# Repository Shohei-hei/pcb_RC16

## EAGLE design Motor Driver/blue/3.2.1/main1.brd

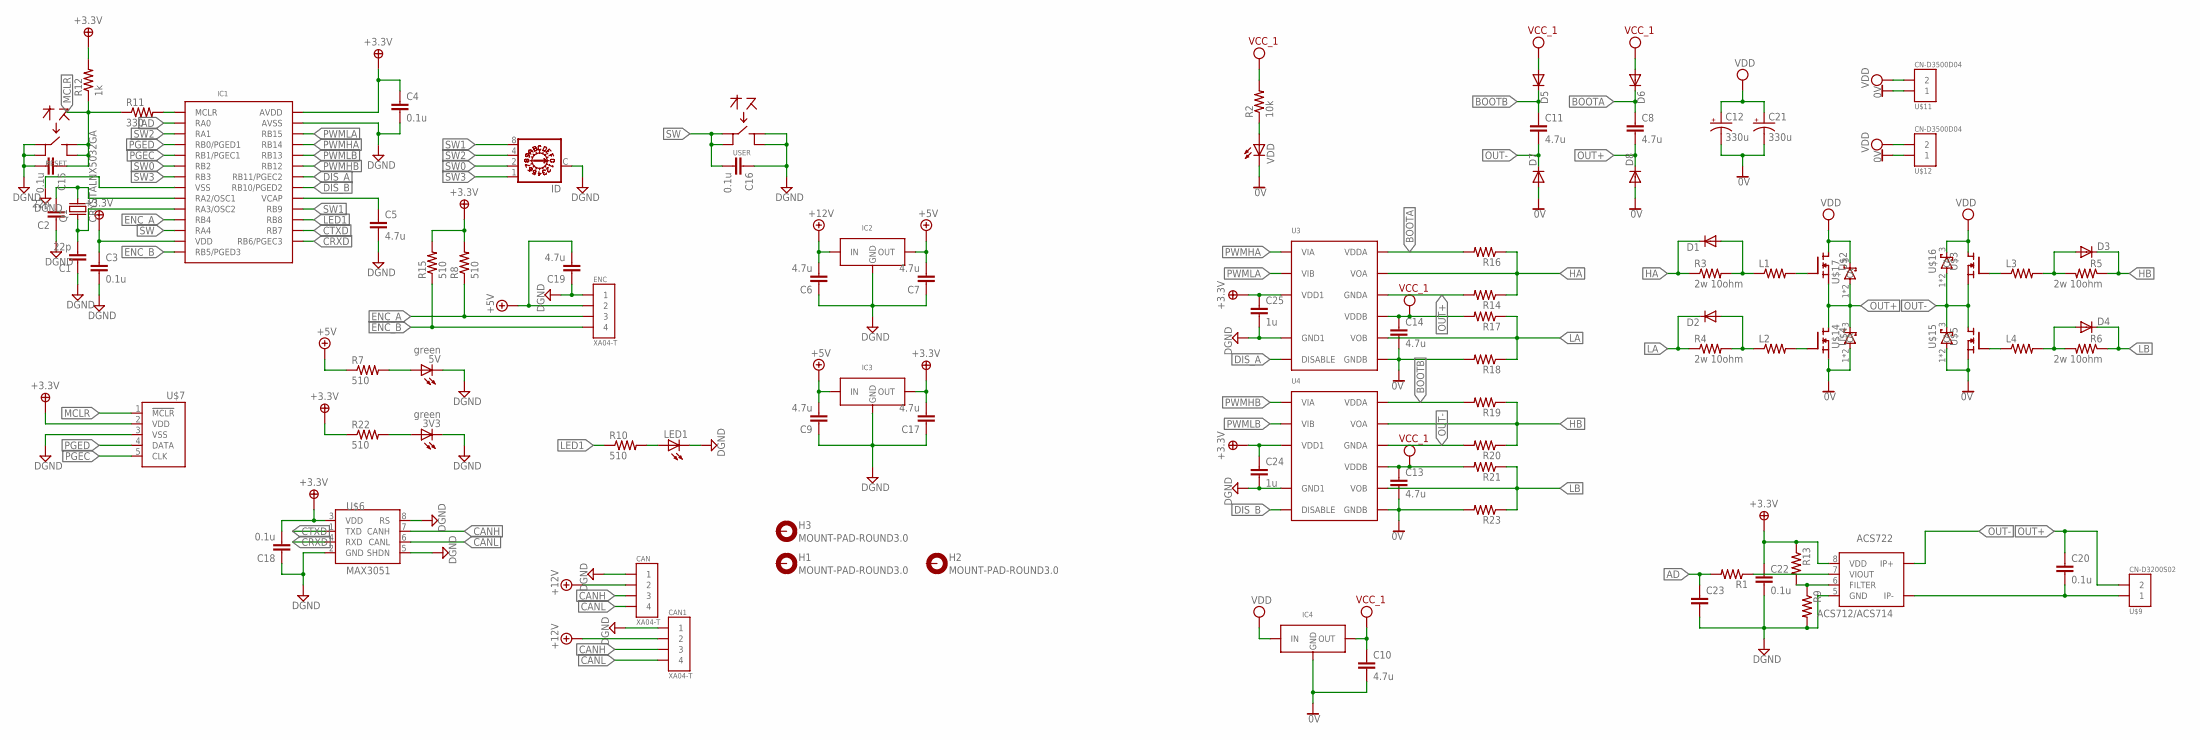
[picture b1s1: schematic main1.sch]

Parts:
3V3, 5V: green; CHIPLED_0603
ACS722: ACS712/ACS714; SOIC8
C1, C2: 22p; C0603K
C3, C4, C15, C16, C18, C20: 0.1u; C0603K
C5, C6, C7, C8, C9, C10, C11, C13, C14, C17, C19: 4.7u; C0805K
C12, C21: 330u; PANASONIC_G
C22: 0.1u; C1206
C23: C-EUC0603K; C0603K
C24, C25: 1u; C0603K
CAN, CAN1: XA04-T; XA04
D1, D2, D3, D4, D5, D6, D7, D8: DIODE-SOD123; SOD123
ENC: XA04-T; XA04
H1, H2, H3: MOUNT-PAD-ROUND3.0; 3,0-PAD
IC1: DSPIC33FJ128MC802; SOIC28
IC2: REGULATER_MIC39100-5.0WS; SOT-223
IC3: REGULATER_AZ1117CR; SOT89
IC4: REGULATER_MIC2940A-5.0WU; TO-263-3
ID: A1353HEX
L1, L2, L3, L4: R-US_R0805; R0805
LED1: LEDCHIPLED_0603; CHIPLED_0603
Q1: CRYSTALNX5032GA; NX5032GA
R1, R9, R13, R14, R16, R17, R18, R19, R20, R21, R23: R-US_R0603; R0603
R2: 10k; R0603
R3, R4, R5, R6: 2w 10ohm; R2512
R7, R8, R10, R15, R22: 510; R0603
R11: 330; R0603
R12: 1k; R0603
RESET: SWITCH_4PALPS; SKRP
U3, U4: ADUM3223_SMD; SOIC16_N
U$1: CN-D3500D04; D-3500D04
U$2, U$3, U$4, U$5: FET_NCH_FDMS86152; PQFN_8L
U$6: MAX3051; SOIC8
U$7: WRITE_FOR_PICT; ZH05
U$9: CN-D3200S02; D-3200S02-S
U$14, U$15, U$16, U$17: SCHOTTKY_BARRIER_DIODE_FSV560; TO-277
USER: SWITCH_4PALPS; SKRP
VDD: LEDCHIPLED_0603; CHIPLED_0603

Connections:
0V: C10.2, C12.-, C13.2, C14.2, C21.-, D7.A, D8.A, IC4.2 (GND), IC4.PAD (GND), R18.2, R23.2, U3.P$9 (GNDB), U4.P$9 (GNDB), U$1.01A (1), U$1.02A (1), U$4.1 (S), U$4.2 (S), U$4.3 (S), U$5.1 (S), U$5.2 (S), U$5.3 (S), U$14.1 (A), U$14.2 (A), U$15.1 (A), U$15.2 (A), VDD.C
3.3V: ACS722.8 (VDD), C3.1, C4.1, C17.2, C18.2, C22.1, C24.1, C25.1, IC1.13 (VDD), IC1.28 (AVDD), IC3.2 (OUT), IC3.P (OUT), R8.2, R12.2, R13.1, R15.2, R22.1, U3.P$3 (VDD1), U3.P$8 (VDD1), U4.P$3 (VDD1), U4.P$8 (VDD1), U$6.3 (VDD), U$7.2 (VDD)
+5V: C7.2, C9.2, C19.2, ENC.PIN2 (2), IC2.3 (OUT), IC3.3 (IN), R7.1
+12V: C6.2, CAN.PIN2 (2), CAN1.PIN2 (2), IC2.1 (IN)
AD: C23.1, IC1.2 (RA0), R1.2
BOOTA: C8.1, D6.C, R16.2, U3.P$16 (VDDA)
BOOTB: C11.1, D5.C, R19.2, U4.P$16 (VDDA)
CANH: CAN.PIN3 (3), CAN1.PIN3 (3), U$6.7 (CANH)
CANL: CAN.PIN4 (4), CAN1.PIN4 (4), U$6.6 (CANL)
CRXD: IC1.15 (RB6/PGEC3), U$6.4 (RXD)
CTXD: IC1.16 (RB7), U$6.1 (TXD)
DGND: 3V3.C, 5V.C, ACS722.5 (GND), C1.1, C2.1, C3.2, C4.2, C5.2, C6.1, C7.1, C9.1, C15.2, C16.1, C17.1, C18.1, C19.1, C22.2, C23.2, C24.2, C25.2, CAN.PIN1 (1), CAN1.PIN1 (1), ENC.PIN1 (1), IC1.8 (VSS), IC1.19 (VSS), IC1.27 (AVSS), IC2.2 (GND), IC2.TAB (GND), IC3.1 (GND), ID.C, LED1.C, R9.2, RESET.1, RESET.2, U3.P$4 (GND1), U4.P$4 (GND1), U$6.2 (GND), U$6.5 (SHDN), U$6.8 (RS), U$7.3 (VSS), USER.3, USER.4
DIS_A: IC1.22 (RB11/PGEC2), U3.P$5 (DISABLE)
DIS_B: IC1.21 (RB10/PGED2), U4.P$5 (DISABLE)
ENC_A: ENC.PIN3 (3), IC1.11 (RB4), R8.1
ENC_B: ENC.PIN4 (4), IC1.14 (RB5/PGED3), R15.1
HA: D1.C, R3.1, R14.1, R16.1, U3.P$15 (VOA)
HB: D3.C, R5.1, R19.1, R20.1, U4.P$15 (VOA)
LA: D2.C, R4.1, R17.1, R18.1, U3.P$10 (VOB)
LB: D4.C, R6.1, R21.1, R23.1, U4.P$10 (VOB)
LED1: IC1.17 (RB8), R10.1
MCLR: C15.1, R11.1, R12.1, RESET.3, RESET.4, U$7.1 (!MCLR)
unnamed: C2.2, IC1.9 (RA2/OSC1), Q1.2
unnamed: C1.2, IC1.10 (RA3/OSC2), Q1.1
unnamed: C5.1, IC1.20 (VCAP)
unnamed: L2.2, U$4.4 (G)
unnamed: R2.1, VDD.A
unnamed: ACS722.7 (VIOUT), R1.1
unnamed: LED1.A, R10.2
unnamed: D1.A, L1.1, R3.2
unnamed: D2.A, L2.1, R4.2
unnamed: 5V.A, R7.2
unnamed: L4.1, U$5.4 (G)
unnamed: D4.A, L4.2, R6.2
unnamed: L3.1, U$3.4 (G)
unnamed: D3.A, L3.2, R5.2
unnamed: ACS722.3 (IP-), ACS722.4 (IP-), C20.2, U$9.1, U$9.P$1 (1)
unnamed: IC1.1 (MCLR), R11.2
unnamed: ACS722.6 (FILTER), R9.1, R13.2
unnamed: 3V3.A, R22.2
unnamed: L1.2, U$2.4 (G)
OUT+: C8.2, C20.1, D8.C, R14.2, U3.P$14 (GNDA), U$2.1 (S), U$2.2 (S), U$2.3 (S), U$4.5 (D), U$4.6 (D), U$4.7 (D), U$4.8 (D), U$4.PAD (D), U$9.2, U$9.P$2 (2), U$14.3 (C), U$17.1 (A), U$17.2 (A)
OUT-: ACS722.1 (IP+), ACS722.2 (IP+), C11.2, D7.C, R20.2, U4.P$14 (GNDA), U$3.1 (S), U$3.2 (S), U$3.3 (S), U$5.5 (D), U$5.6 (D), U$5.7 (D), U$5.8 (D), U$5.PAD (D), U$15.3 (C), U$16.1 (A), U$16.2 (A)
PGEC: IC1.5 (RB1/PGEC1), U$7.5 (CLK)
PGED: IC1.4 (RB0/PGED1), U$7.4 (DATA)
PWMHA: IC1.25 (RB14), U3.P$1 (VIA)
PWMHB: IC1.23 (RB12), U4.P$1 (VIA)
PWMLA: IC1.26 (RB15), U3.P$2 (VIB)
PWMLB: IC1.24 (RB13), U4.P$2 (VIB)
SW: C16.2, IC1.12 (RA4), USER.1, USER.2
SW0: IC1.6 (RB2), ID.2
SW1: IC1.18 (RB9), ID.8
SW2: IC1.3 (RA1), ID.4
SW3: IC1.7 (RB3), ID.1
VCC_1: C10.1, C13.1, C14.1, D5.A, D6.A, IC4.3 (OUT), R2.2, R17.2, R21.2, U3.P$11 (VDDB), U4.P$11 (VDDB)
VDD: C12.+, C21.+, IC4.1 (IN), U$1.01B (2), U$1.02B (2), U$2.5 (D), U$2.6 (D), U$2.7 (D), U$2.8 (D), U$2.PAD (D), U$3.5 (D), U$3.6 (D), U$3.7 (D), U$3.8 (D), U$3.PAD (D), U$16.3 (C), U$17.3 (C)

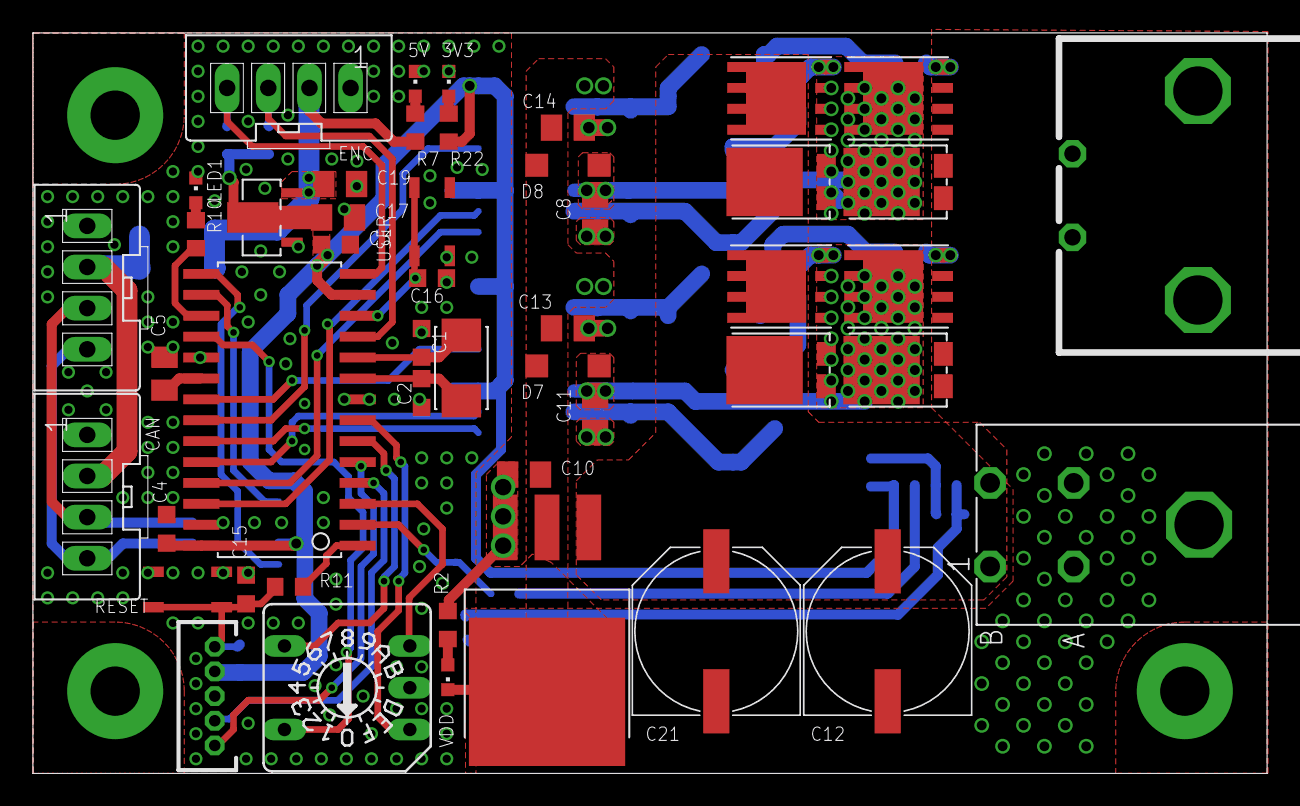
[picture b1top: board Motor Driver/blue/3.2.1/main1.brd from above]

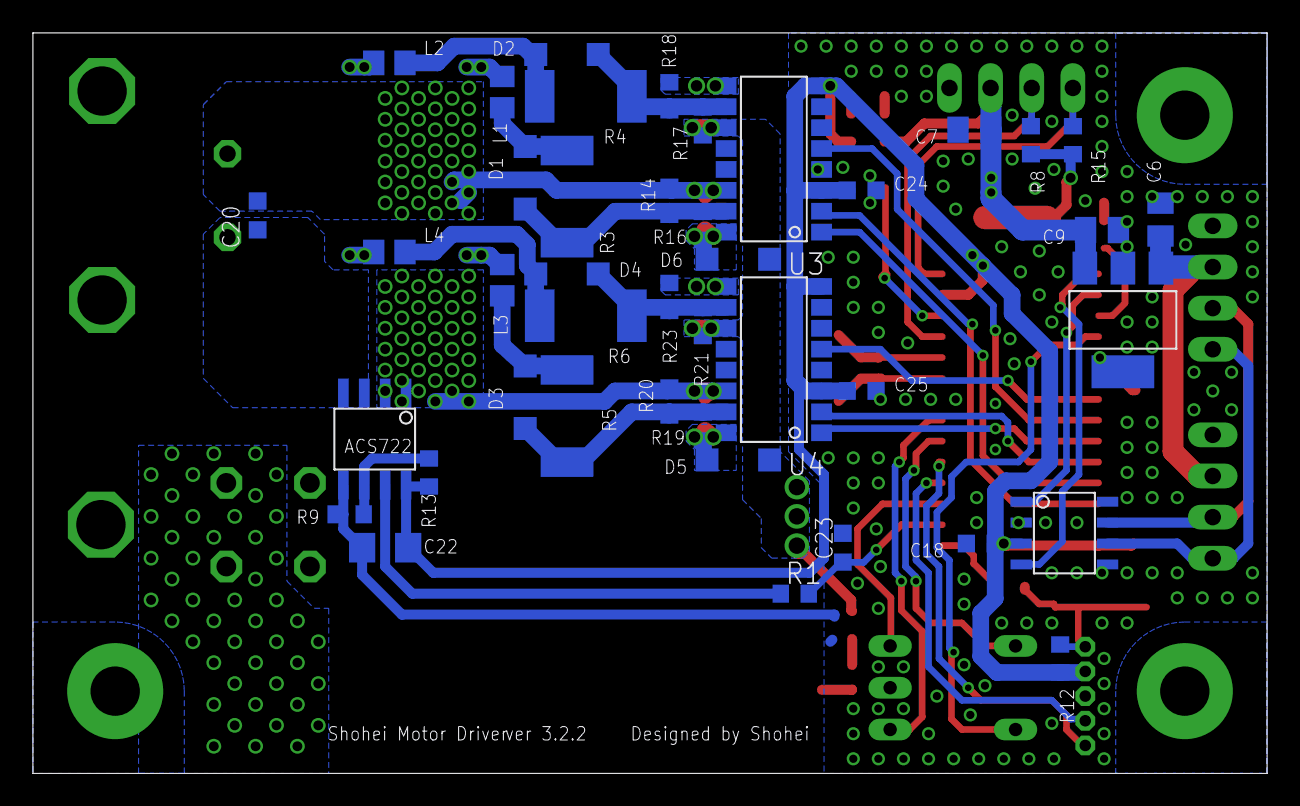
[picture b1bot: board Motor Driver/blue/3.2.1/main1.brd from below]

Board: 2 copper layers, 75.0 x 45.0 mm, 93 parts (42 on the bottom side), 56 nets.

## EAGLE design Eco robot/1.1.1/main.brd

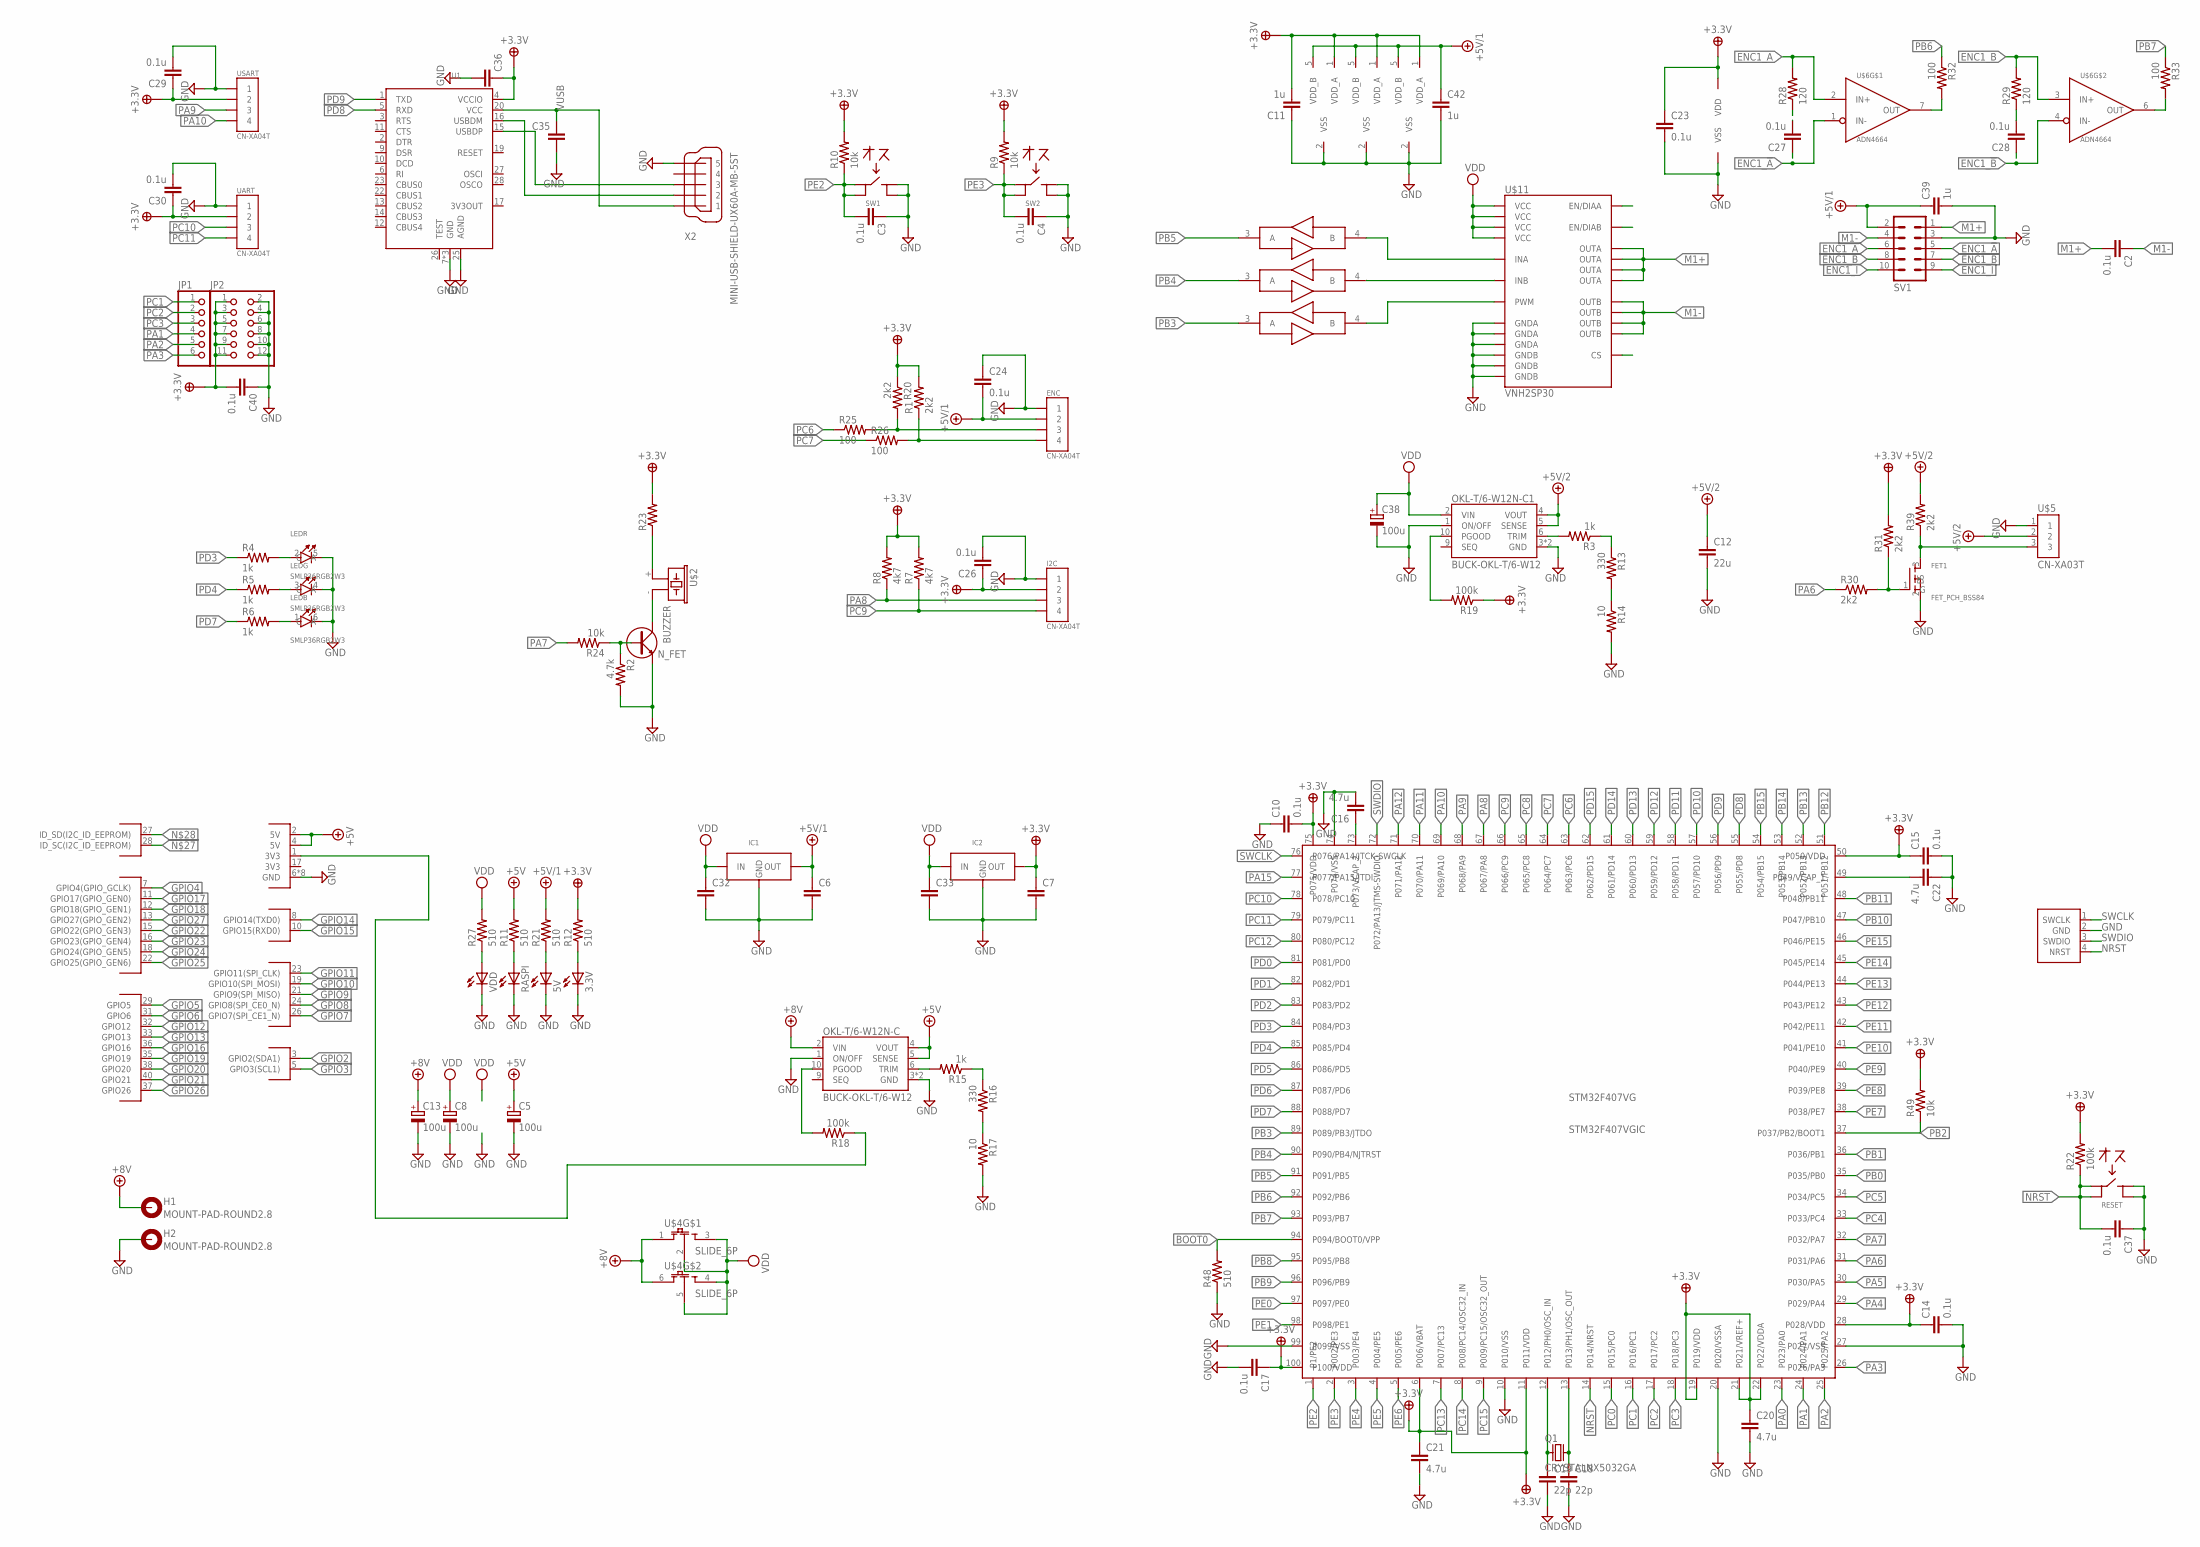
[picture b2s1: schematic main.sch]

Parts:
3.3V, 5V: LEDCHIPLED_0603; CHIPLED_0603
C2, C3, C4, C10, C14, C15, C17, C23, C27, C28, C37: 0.1u; C0603K
C5, C13: 100u; PANASONIC_C
C6, C7, C32, C33: C-EUC0805K; C0805K
C8, C38: 100u; PANASONIC_D
C11, C39, C42: 1u; C0603K
C12: 22u; C0805K
C16, C20, C21, C22: 4.7u; C0805K
C18, C19: 22p; C0603K
C24, C26, C29, C30: 0.1u; C0805
C35, C36: C-EUC0603K; C0603K
C40: 0.1u; C0805K
ENC: CN-XA04T; XA04
FET1: FET_PCH_BSS84; SOT-23-3
H1, H2: MOUNT-PAD-ROUND2.8; 2,8-PAD
I2C: CN-XA04T; XA04
IC1, IC2: REGULATERLM1058; SOT-223
JP1: PINHD-1X06_2.54-S; 1X06-S
JP2: PINHD-2X06_2.54; 2X06
LED: SMLP36RGB2W3; 0604(6PIN)
N_FET: TR_NTR; SOT-23-3
OKL-T/6-W12N-C, OKL-T/6-W12N-C1: BUCK-OKL-T/6-W12
Q1: CRYSTALNX5032GA; NX5032GA
R1, R20, R30, R31, R39: 2k2; R0603
R2: 4.7k; R0603
R3, R15: 1k; R0603
R4, R5, R6: 1k; R0402
R7, R8: 4k7; R0603
R9, R10, R24, R49: 10k; R0603
R11, R12, R21, R27, R48: 510; R0603
R13, R16: 330; R0603
R14, R17: 10; R0603
R18, R19, R22: 100k; R0603
R23: R-US_R0603; R0603
R25, R26, R32, R33: 100; R0603
R28, R29: 120; R0603
RASPI: LEDCHIPLED_0603; CHIPLED_0603
RESET: SWITCH_4PALPS; SKRP
STM32F407VG: STM32F407VGIC; LQFP100
SV1: ML10_T; ML10
SW1, SW2: SWITCH_4PALPS; SKRP
U1: FT232RL; SSOP28
U$1: RASPBERRY_PAI2_B; PAI_2_B_RS
U$2: BUZZER; SMT-0440-S-R
U$3: WRITE_FOR_STM32FXT; ZH05
U$4: SLIDE_6P; SSW-SMD
U$5: CN-XA03T; XA03
U$6: ADN4664; SOIC8
U$7, U$9, U$10: MAX3370; SOT-353/SC-70-5
U$11: VNH2SP30
UART: CN-XA04T; XA04
USART: CN-XA04T; XA04
VDD: LEDCHIPLED_0603; CHIPLED_0603
X2: MINI-USB-SHIELD-UX60A-MB-5ST; UX60A-MB-5ST

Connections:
3.3V: C7.1, C10.2, C11.2, C14.1, C15.1, C17.1, C20.1, C21.1, C23.1, C26.1, C29.1, C30.1, C36.1, C40.2, I2C.PIN2 (2), IC2.2 (OUT), IC2.4 (OUT), JP2.1, JP2.3, JP2.5, JP2.7, JP2.9, JP2.11, R1.2, R7.2, R8.2, R9.2, R10.2, R12.2, R19.1, R20.1, R22.2, R23.2, R31.2, R49.2, STM32F407VG.6 (P006/VBAT), STM32F407VG.11 (P011/VDD), STM32F407VG.19 (P019/VDD), STM32F407VG.21 (P021/VREF+), STM32F407VG.22 (P022/VDDA), STM32F407VG.28 (P028/VDD), STM32F407VG.50 (P050/VDD), STM32F407VG.75 (P075/VDD), STM32F407VG.100 (P100/VDD), U1.4 (VCCIO), U$6.8 (VDD), U$7.1 (VDD_A), U$9.1 (VDD_A), U$10.1 (VDD_A), UART.PIN2 (2), USART.PIN2 (2)
+5V: C5.+, OKL-T/6-W12N-C.4 (VOUT), OKL-T/6-W12N-C.5 (SENSE), R11.2, U$1.2 (5V), U$1.4 (5V)
+5V/1: C6.1, C24.2, C39.1, C42.1, ENC.PIN2 (2), IC1.2 (OUT), IC1.4 (OUT), R21.2, SV1.2, U$7.5 (VDD_B), U$9.5 (VDD_B), U$10.5 (VDD_B)
+5V/2: C12.1, OKL-T/6-W12N-C1.4 (VOUT), OKL-T/6-W12N-C1.5 (SENSE), R39.2, U$5.2
+8V: C13.+, H1.B2,8, OKL-T/6-W12N-C.2 (VIN), U$4.1, U$4.6
BOOT0: R48.2, STM32F407VG.94 (P094/BOOT0/VPP)
ENC1_!A: C27.1, SV1.5, U$6.1 (IN-)
ENC1_!B: C28.1, SV1.7, U$6.4 (IN-)
ENC1_!I: SV1.9
ENC1_A: R28.2, SV1.6, U$6.2 (IN+)
ENC1_B: R29.2, SV1.8, U$6.3 (IN+)
ENC1_I: SV1.10
GND: 3.3V.C, 5V.C, C3.1, C4.1, C5.-, C6.2, C7.2, C8.-, C10.1, C11.1, C12.2, C13.-, C14.2, C15.2, C16.2, C17.2, C18.2, C19.2, C20.2, C21.2, C22.1, C23.2, C24.1, C26.2, C29.2, C30.2, C32.2, C33.2, C35.2, C36.2, C37.1, C38.-, C39.2, C40.1, C42.2, ENC.PIN1 (1), FET1.2 (S), H2.B2,8, I2C.PIN1 (1), IC1.1 (GND), IC2.1 (GND), JP2.2, JP2.4, JP2.6, JP2.8, JP2.10, JP2.12, LED.4 (C), LED.5 (C), LED.6 (C), N_FET.2 (E), OKL-T/6-W12N-C.1 (ON/OFF), OKL-T/6-W12N-C.3 (GND), OKL-T/6-W12N-C.7 (GND), OKL-T/6-W12N-C1.1 (ON/OFF), OKL-T/6-W12N-C1.3 (GND), OKL-T/6-W12N-C1.7 (GND), R2.2, R14.2, R17.2, R48.1, RASPI.C, RESET.3, RESET.4, STM32F407VG.10 (P010/VSS), STM32F407VG.20 (P020/VSSA), STM32F407VG.27 (P027/VSS), STM32F407VG.74 (P074/VSS), STM32F407VG.99 (P099/VSS), SV1.3, SW1.3, SW1.4, SW2.3, SW2.4, U1.7 (GND), U1.18 (GND), U1.21 (GND), U1.25 (AGND), U$1.6 (GND), U$1.9 (GND), U$1.14 (GND), U$1.20 (GND), U$1.25 (GND), U$1.30 (GND), U$1.34 (GND), U$1.39 (GND), U$3.2 (GND), U$5.1, U$6.5 (VSS), U$7.2 (VSS), U$9.2 (VSS), U$10.2 (VSS), U$11.18 (GNDB), U$11.19 (GNDB), U$11.20 (GNDB), U$11.26 (GNDA), U$11.27 (GNDA), U$11.28 (GNDA), UART.PIN1 (1), USART.PIN1 (1), VDD.C, X2.5
GPIO2: U$1.3 (GPIO2(SDA1))
GPIO3: U$1.5 (GPIO3(SCL1))
GPIO4: U$1.7 (GPIO4(GPIO_GCLK))
GPIO5: U$1.29 (GPIO5)
GPIO6: U$1.31 (GPIO6)
GPIO7: U$1.26 (GPIO7(SPI_CE1_N))
GPIO8: U$1.24 (GPIO8(SPI_CE0_N))
GPIO9: U$1.21 (GPIO9(SPI_MISO))
GPIO10: U$1.19 (GPIO10(SPI_MOSI))
GPIO11: U$1.23 (GPIO11(SPI_CLK))
GPIO12: U$1.32 (GPIO12)
GPIO13: U$1.33 (GPIO13)
GPIO14: U$1.8 (GPIO14(TXD0))
GPIO15: U$1.10 (GPIO15(RXD0))
GPIO16: U$1.36 (GPIO16)
GPIO17: U$1.11 (GPIO17(GPIO_GEN0))
GPIO18: U$1.12 (GPIO18(GPIO_GEN1))
GPIO19: U$1.35 (GPIO19)
GPIO20: U$1.38 (GPIO20)
GPIO21: U$1.40 (GPIO21)
GPIO22: U$1.15 (GPIO22(GPIO_GEN3))
GPIO23: U$1.16 (GPIO23(GPIO_GEN4))
GPIO24: U$1.18 (GPIO24(GPIO_GEN5))
GPIO25: U$1.22 (GPIO25(GPIO_GEN6))
GPIO26: U$1.37 (GPIO26)
GPIO27: U$1.13 (GPIO27(GPIO_GEN2))
M1+: C2.2, SV1.1, U$11.1 (OUTA), U$11.25 (OUTA), U$11.30 (OUTA), U$11.SLUG3 (OUTA)
M1-: C2.1, SV1.4, U$11.15 (OUTB), U$11.16 (OUTB), U$11.21 (OUTB), U$11.SLUG2 (OUTB)
unnamed: ENC.PIN3 (3), R20.2, R25.2
unnamed: OKL-T/6-W12N-C1.6 (TRIM), R3.2
unnamed: LED.2 (A), R4.2
unnamed: LED.3 (A), R5.2
unnamed: LED.1 (A), R6.2
unnamed: N_FET.3 (C), U$2.- (2)
unnamed: C16.1, STM32F407VG.73 (P073/VCAP_2)
unnamed: R23.1, U$2.+ (1)
unnamed: R11.1, RASPI.A
unnamed: R3.1, R13.1
unnamed: N_FET.1 (B), R2.1, R24.1
unnamed: C27.2, R28.1
unnamed: OKL-T/6-W12N-C.6 (TRIM), R15.2
unnamed: R13.2, R14.1
unnamed: 3.3V.A, R12.1
unnamed: U$7.4 (B), U$11.8 (PWM)
unnamed: U1.15 (USBDP), X2.3
unnamed: ENC.PIN4 (4), R1.1, R26.2
unnamed: U1.16 (USBDM), X2.2
unnamed: R15.1, R16.1
unnamed: U$9.4 (B), U$11.11 (INB)
unnamed: R16.2, R17.1
unnamed: OKL-T/6-W12N-C.10 (PGOOD), R18.2
unnamed: C22.2, STM32F407VG.49 (P049/VCAP_1)
unnamed: 5V.A, R21.1
unnamed: R27.1, VDD.A
unnamed: C28.2, R29.1
unnamed: OKL-T/6-W12N-C1.10 (PGOOD), R19.2
unnamed: U$10.4 (B), U$11.5 (INA)
unnamed: FET1.3 (D), R39.1, U$5.3
unnamed: FET1.1 (G), R30.2, R31.1
unnamed: R18.1, U$1.1 (3V3)
unnamed: R32.2, U$6.7 (OUT)
unnamed: R33.2, U$6.6 (OUT)
NRST: C37.2, R22.1, RESET.1, RESET.2, STM32F407VG.14 (P014/NRST), U$3.4 (NRST)
PA0: STM32F407VG.23 (P023/PA0)
PA1: JP1.4, STM32F407VG.24 (P024/PA1)
PA2: JP1.5, STM32F407VG.25 (P025/PA2)
PA3: JP1.6, STM32F407VG.26 (P026/PA3)
PA4: STM32F407VG.29 (P029/PA4)
PA5: STM32F407VG.30 (P030/PA5)
PA6: R30.1, STM32F407VG.31 (P031/PA6)
PA7: R24.2, STM32F407VG.32 (P032/PA7)
PA8: I2C.PIN3 (3), R8.1, STM32F407VG.67 (P067/PA8)
PA9: STM32F407VG.68 (P068/PA9), USART.PIN3 (3)
PA10: STM32F407VG.69 (P069/PA10), USART.PIN4 (4)
PA11: STM32F407VG.70 (P070/PA11)
PA12: STM32F407VG.71 (P071/PA12)
PA15: STM32F407VG.77 (P077/PA15/JTDI)
PB0: STM32F407VG.35 (P035/PB0)
PB1: STM32F407VG.36 (P036/PB1)
PB2: R49.1, STM32F407VG.37 (P037/PB2/BOOT1)
PB3: STM32F407VG.89 (P089/PB3/JTDO), U$7.3 (A)
PB4: STM32F407VG.90 (P090/PB4/NJTRST), U$9.3 (A)
PB5: STM32F407VG.91 (P091/PB5), U$10.3 (A)
PB6: R32.1, STM32F407VG.92 (P092/PB6)
PB7: R33.1, STM32F407VG.93 (P093/PB7)
PB8: STM32F407VG.95 (P095/PB8)
PB9: STM32F407VG.96 (P096/PB9)
PB10: STM32F407VG.47 (P047/PB10)
PB11: STM32F407VG.48 (P048/PB11)
PB12: STM32F407VG.51 (P051/PB12)
PB13: STM32F407VG.52 (P052/PB13)
PB14: STM32F407VG.53 (P053/PB14)
PB15: STM32F407VG.54 (P054/PB15)
PC0: STM32F407VG.15 (P015/PC0)
PC1: JP1.1, STM32F407VG.16 (P016/PC1)
PC2: JP1.2, STM32F407VG.17 (P017/PC2)
PC3: JP1.3, STM32F407VG.18 (P018/PC3)
PC4: STM32F407VG.33 (P033/PC4)
PC5: STM32F407VG.34 (P034/PC5)
PC6: R25.1, STM32F407VG.63 (P063/PC6)
PC7: R26.1, STM32F407VG.64 (P064/PC7)
PC8: STM32F407VG.65 (P065/PC8)
PC9: I2C.PIN4 (4), R7.1, STM32F407VG.66 (P066/PC9)
PC10: STM32F407VG.78 (P078/PC10), UART.PIN3 (3)
PC11: STM32F407VG.79 (P079/PC11), UART.PIN4 (4)
PC12: STM32F407VG.80 (P080/PC12)
PC13: STM32F407VG.7 (P007/PC13)
PC14: STM32F407VG.8 (P008/PC14/OSC32_IN)
PC15: STM32F407VG.9 (P009/PC15/OSC32_OUT)
PD0: STM32F407VG.81 (P081/PD0)
PD1: STM32F407VG.82 (P082/PD1)
PD2: STM32F407VG.83 (P083/PD2)
PD3: R4.1, STM32F407VG.84 (P084/PD3)
PD4: R5.1, STM32F407VG.85 (P085/PD4)
PD5: STM32F407VG.86 (P086/PD5)
PD6: STM32F407VG.87 (P087/PD6)
PD7: R6.1, STM32F407VG.88 (P088/PD7)
PD8: STM32F407VG.55 (P055/PD8), U1.5 (RXD)
PD9: STM32F407VG.56 (P056/PD9), U1.1 (TXD)
PD10: STM32F407VG.57 (P057/PD10)
PD11: STM32F407VG.58 (P058/PD11)
PD12: STM32F407VG.59 (P059/PD12)
PD13: STM32F407VG.60 (P060/PD13)
PD14: STM32F407VG.61 (P061/PD14)
PD15: STM32F407VG.62 (P062/PD15)
PE0: STM32F407VG.97 (P097/PE0)
PE1: STM32F407VG.98 (P098/PE1)
PE2: C3.2, R10.1, STM32F407VG.1 (P1/PE2), SW1.1, SW1.2
PE3: C4.2, R9.1, STM32F407VG.2 (P002/PE3), SW2.1, SW2.2
PE4: STM32F407VG.3 (P003/PE4)
PE5: STM32F407VG.4 (P004/PE5)
PE6: STM32F407VG.5 (P005/PE6)
PE7: STM32F407VG.38 (P038/PE7)
PE8: STM32F407VG.39 (P039/PE8)
PE9: STM32F407VG.40 (P040/PE9)
PE10: STM32F407VG.41 (P041/PE10)
PE11: STM32F407VG.42 (P042/PE11)
PE12: STM32F407VG.43 (P043/PE12)
PE13: STM32F407VG.44 (P044/PE13)
PE14: STM32F407VG.45 (P045/PE14)
PE15: STM32F407VG.46 (P046/PE15)
PH0: C19.1, Q1.1, STM32F407VG.12 (P012/PH0/OSC_IN)
PH1: C18.1, Q1.2, STM32F407VG.13 (P013/PH1/OSC_OUT)
SWCLK: STM32F407VG.76 (P076/PA14/JTCK-SWCLK), U$3.1 (SWCLK)
SWDIO: STM32F407VG.72 (P072/PA13/JTMS-SWDIO), U$3.3 (SWDIO)
VDD: C8.+, C32.1, C33.1, C38.+, IC1.3 (IN), IC2.3 (IN), OKL-T/6-W12N-C1.2 (VIN), R27.2, U$4.2, U$4.3, U$4.4, U$4.5, U$11.3 (VCC), U$11.13 (VCC), U$11.23 (VCC), U$11.SLUG1 (VCC)
VUSB: C35.1, U1.20 (VCC), X2.1

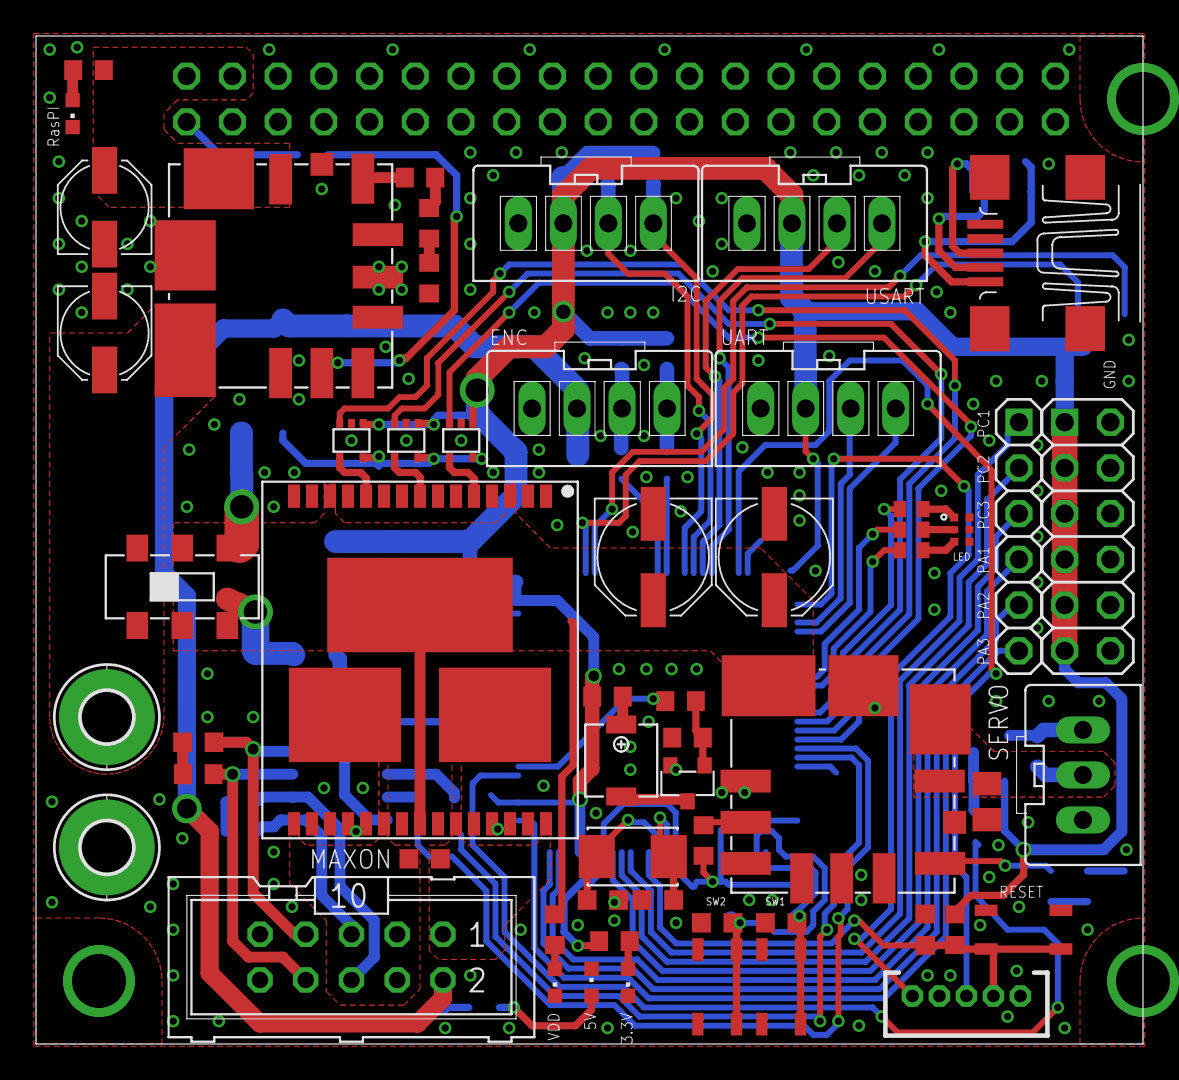
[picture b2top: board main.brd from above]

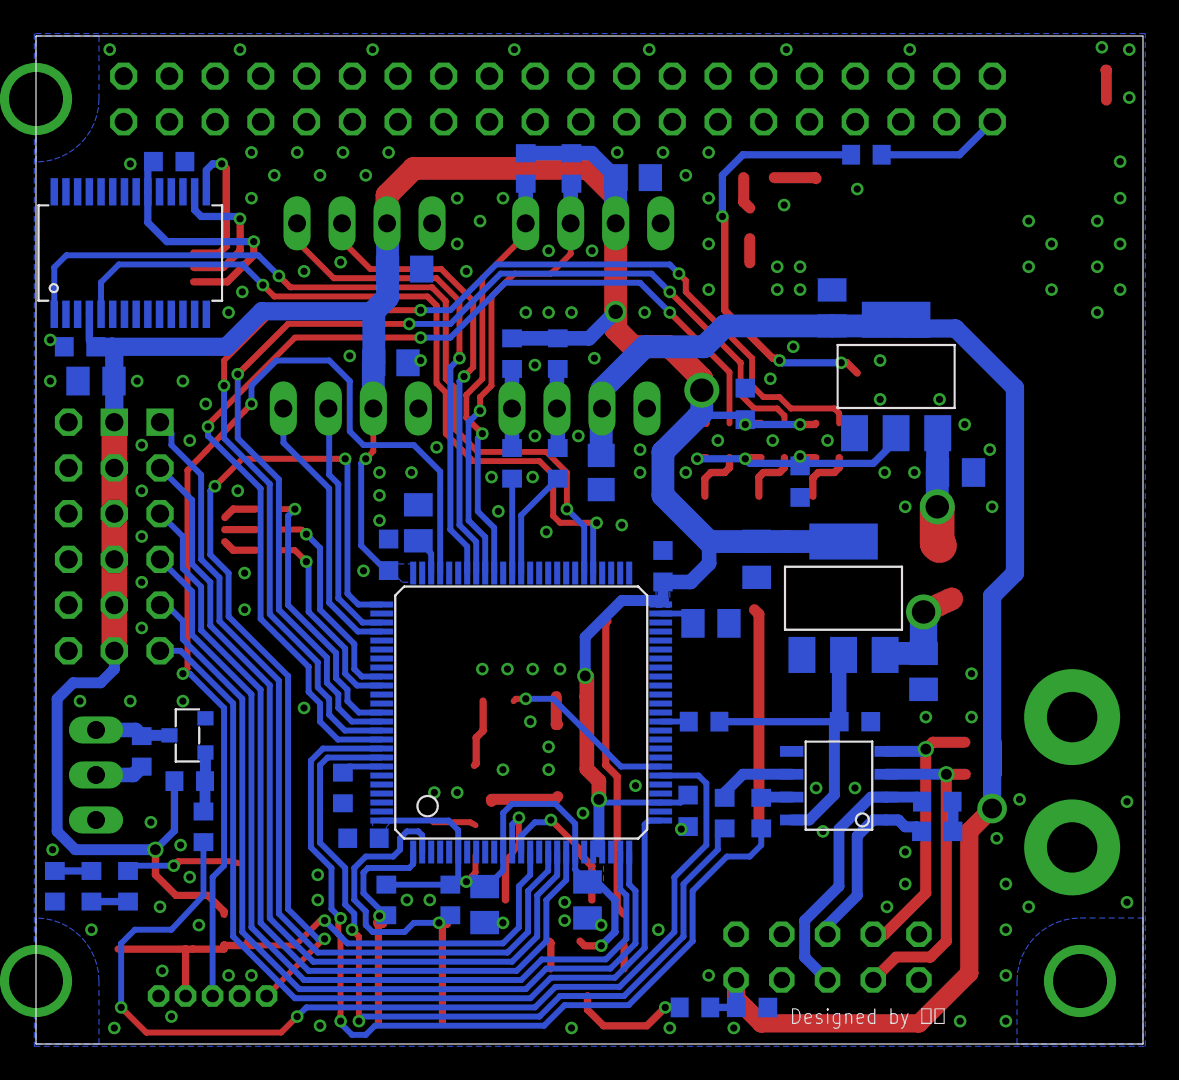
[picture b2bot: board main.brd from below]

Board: 2 copper layers, 61.5 x 56.0 mm, 109 parts (51 on the bottom side), 83 nets.

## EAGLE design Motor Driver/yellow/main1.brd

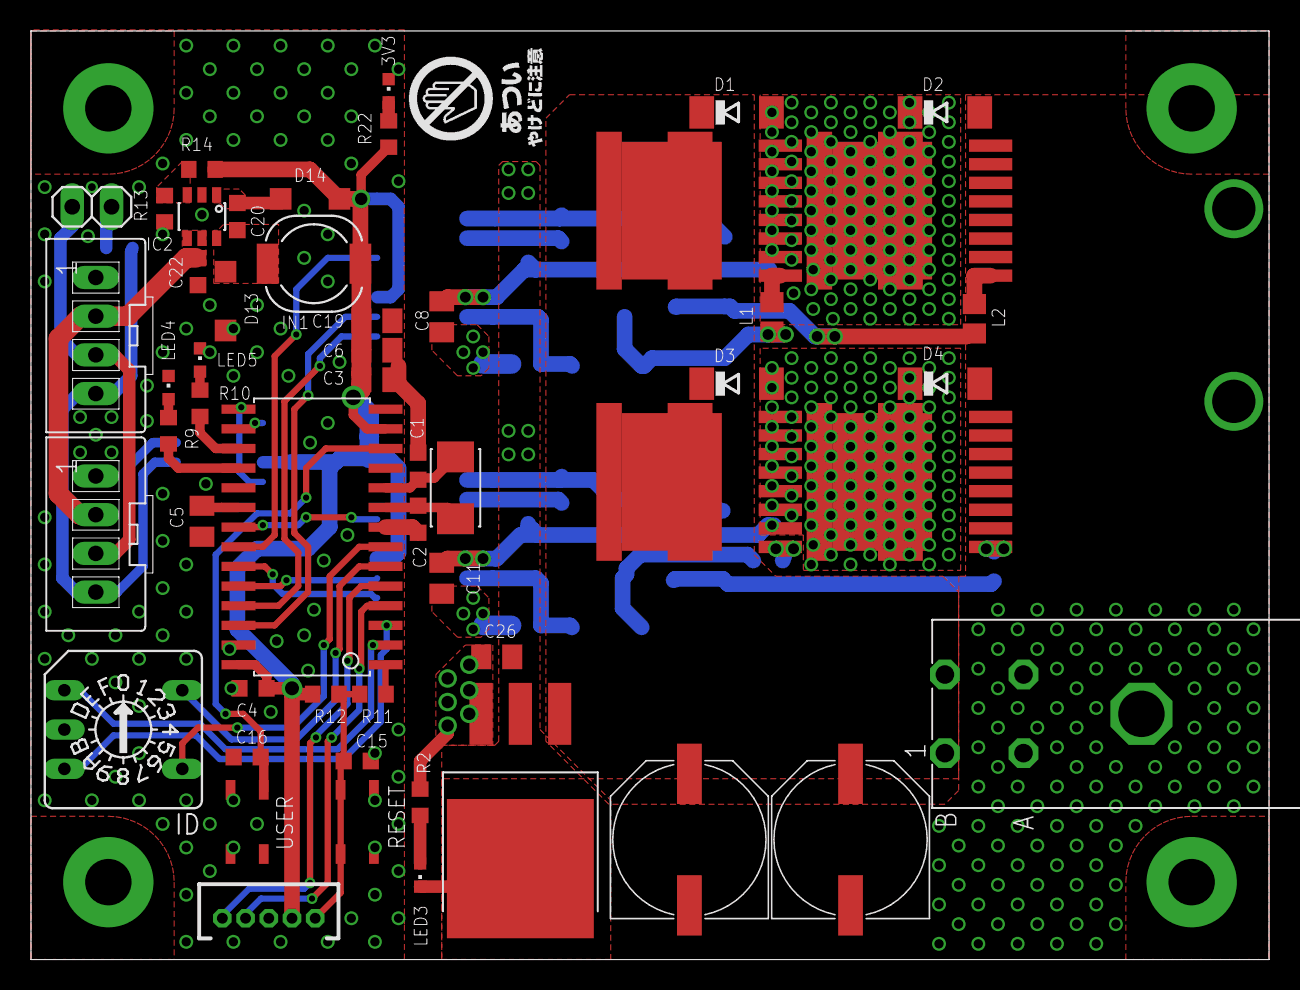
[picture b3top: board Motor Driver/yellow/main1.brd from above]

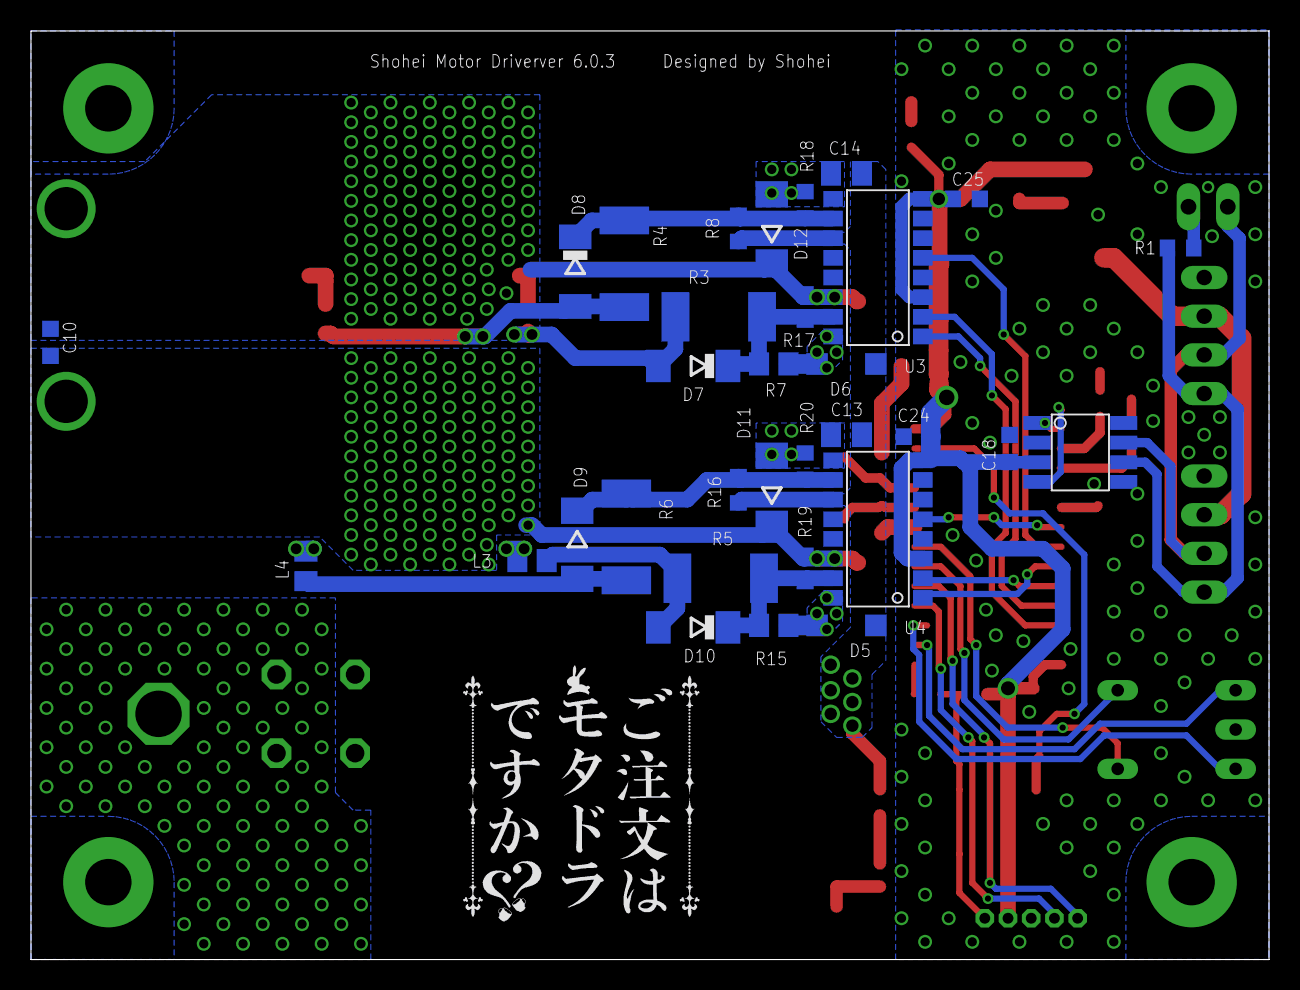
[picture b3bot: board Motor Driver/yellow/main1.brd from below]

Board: 2 copper layers, 80.0 x 60.0 mm, 91 parts (33 on the bottom side), 54 nets.

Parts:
3V3: CHIPLED_0603
C1, C2: 22p; C0603K
C3, C13, C14: 0.1u; C0805K
C4, C10, C15, C16, C18, C20, C24, C25: 0.1u; C0603K
C5, C6, C8, C11, C19, C26: 4.7u; C0805K
C12, C21: PANASONIC_G
C22: 4.7u; C0603K
CN2, CN3: XA04-T; XA04
D1, D2, D3, D4: SBD; SOD106-R
D5, D6, D13, D14: SOD123
D7, D8, D10: SOD106-R
D9, D11, D12: SOD106A-R
H1, H2, H3, H4: MOUNT-PAD-ROUND3.0; 3,0-PAD
IC1: DSPIC33FJ32MC302/64MC202/64MC802/128MC202/128MC802; SOIC28
IC2: LT1616
IC3: REGULATER_MIC2940A; TO-263-3
ID: A1353HEX
IN1: #A921CY100M
JP3: 1X02
L1, L2, L3, L4: R0805
LED3, LED4, LED5: CHIPLED_0603
Q2: CRYSTALNX5032GA; NX5032GA
R1: 120; R0603
R2, R12: 1k; R0603
R3, R4, R5, R6: 2w 10ohm; R2512
R7, R15: 510; R0805
R8, R9, R10, R16, R17, R18, R19, R20, R22: 510; R0603
R11: 330; R0603
R13: 10k; R0603
R14: 33k; R0603
SW1, SW2: SWITCH_4PALPS; SKRP
U3, U4: SOIC16_N
U$1: CN-D3500D04; D-3500D04
U$2, U$3, U$4, U$5: FET_NCHFDBL0065N40; MO-299A
U$6: MAX3051; SOIC8
U$7: WRITE_FOR_PICT; ZH05
U$10: LOGO_ATSUI; LOGO008
U$11: LOGO_GOTIUSA2; LOGO011

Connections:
0V: C12.-, C13.2, C14.2, C21.-, C26.2, D2.A, D4.A, D11.A, D12.A, IC3.2, IC3.PAD, LED3.C, R18.2, R20.2, U3.P$9, U4.P$9, U$1.01A, U$1.02A, U$3.2, U$3.3, U$3.4, U$3.5, U$3.6, U$3.7, U$3.8, U$5.2, U$5.3, U$5.4, U$5.5, U$5.6, U$5.7, U$5.8
3.3V: C3.1, C4.1, C6.2, C18.2, C19.2, C24.1, C25.1, D14.A, IC1.13, IC1.28, IN1.2, R12.2, R14.1, R22.1, U3.P$3, U3.P$8, U4.P$3, U4.P$8, U$6.3, U$7.2
+10V: C22.2, CN2.PIN2, CN3.PIN2, IC2.SHDN, IC2.VIN
BOOTA: C8.1, D6.C, R7.2, U3.P$16
BOOTB: C11.1, D5.C, R15.2, U4.P$16
CANH: CN2.PIN3, CN3.PIN3, JP3.2, U$6.7
CANL: CN2.PIN4, CN3.PIN4, R1.1, U$6.6
CRXD: IC1.15, U$6.4
CTXD: IC1.16, U$6.1
DGND: 3V3.C, C1.1, C2.1, C3.2, C4.2, C5.2, C6.1, C15.2, C16.1, C18.1, C19.1, C22.1, C24.2, C25.2, CN2.PIN1, CN3.PIN1, D13.A, IC1.8, IC1.19, IC1.27, IC2.GND, ID.C, LED4.C, LED5.C, R13.1, SW1.1, SW1.2, SW2.3, SW2.4, U3.P$4, U4.P$4, U$6.2, U$6.5, U$6.8, U$7.3
DIS_A: IC1.22, U3.P$5
DIS_B: IC1.21, U4.P$5
HA: D7.C, R3.1, R7.1, R17.1, U3.P$15
HB: D10.C, R5.1, R15.1, R19.1, U4.P$15
LA: D8.C, R4.1, R8.1, R18.1, U3.P$10
LB: D9.C, R6.1, R16.1, R20.1, U4.P$10
LED0: IC1.18, R9.1
LED1: IC1.17, R10.1
MCLR: C15.1, R11.1, R12.1, SW1.3, SW1.4, U$7.1
unnamed: C2.2, IC1.9, Q2.2
unnamed: C1.2, IC1.10, Q2.1
unnamed: C5.1, IC1.20
unnamed: JP3.1, R1.2
unnamed: LED3.A, R2.1
unnamed: LED4.A, R9.2
unnamed: LED5.A, R10.2
unnamed: L1.2, U$2.1
unnamed: D8.A, L2.1, R4.2
unnamed: L2.2, U$3.1
unnamed: D9.A, L4.2, R6.2
unnamed: L4.1, U$5.1
unnamed: D10.A, L3.2, R5.2
unnamed: L3.1, U$4.1
unnamed: IC1.1, R11.2
unnamed: 3V3.A, R22.2
unnamed: D7.A, L1.1, R3.2
unnamed: C20.2, D13.C, IC2.SW, IN1.1
unnamed: IC2.FB, R13.2, R14.2
unnamed: C20.1, D14.C, IC2.BOOST
OUT+: C8.2, C10.2, D1.A, D2.C, D12.C, R17.2, U3.P$14, U$2.2, U$2.3, U$2.4, U$2.5, U$2.6, U$2.7, U$2.8, U$3.PAD1, U$3.PAD2, U$3.PAD3, U$3.PAD4
OUT-: C10.1, C11.2, D3.A, D4.C, D11.C, R19.2, U4.P$14, U$4.2, U$4.3, U$4.4, U$4.5, U$4.6, U$4.7, U$4.8, U$5.PAD1, U$5.PAD2, U$5.PAD3, U$5.PAD4
PGEC: IC1.5, U$7.5
PGED: IC1.4, U$7.4
PWMHA: IC1.25, U3.P$1
PWMHB: IC1.23, U4.P$1
PWMLA: IC1.26, U3.P$2
PWMLB: IC1.24, U4.P$2
SW: C16.2, IC1.12, SW2.1
SW0: IC1.7, ID.2
SW1: IC1.6, ID.8
SW2: IC1.3, ID.4
SW3: IC1.2, ID.1
VCC_1: C13.1, C14.1, C26.1, D5.A, D6.A, IC3.3, R2.2, R8.2, R16.2, U3.P$11, U4.P$11
VDD: C12.+, C21.+, D1.C, D3.C, IC3.1, U$1.01B, U$1.02B, U$2.PAD1, U$2.PAD2, U$2.PAD3, U$2.PAD4, U$4.PAD1, U$4.PAD2, U$4.PAD3, U$4.PAD4
